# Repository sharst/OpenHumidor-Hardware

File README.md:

# OpenHumidor-Hardware
KiCad files of the OpenHumidor sensor PCB.
Files for 3D-printed humidifier parts, enclosures of the sensor board, etc.

Copyright 2016 Simon Harst

These files are licenced under the GPL v3 Licence, see LICENCE file.

I have included former versions of the PCB in separate folders. 

Versions 2 and 3 were created using the free version of EAGLE. Since version 4, boards are created with KICAD. 

## Ordering PCBs
The current version of the board is v0.6-mega. I'm currently testing all functions but minor bugs might still occur. If you're interested in trying out this project, you should consider contacting me.

So far, I have only ordered with two companies: 
* [PCB-pool](www.pcb-pool.de), located in Germany, the cheapest option takes about 2 weeks incl. shipping, you can directly upload the .kicad_pcb-file. 
* [Seeed Studio](http://www.seeedstudio.com/service/index.php?r=pcb), located in China and a lot cheaper (~14Euros for 10 pcbs). Takes about a month including shipping. You need to upload the .zip-file that's included in the gerber/ folder.

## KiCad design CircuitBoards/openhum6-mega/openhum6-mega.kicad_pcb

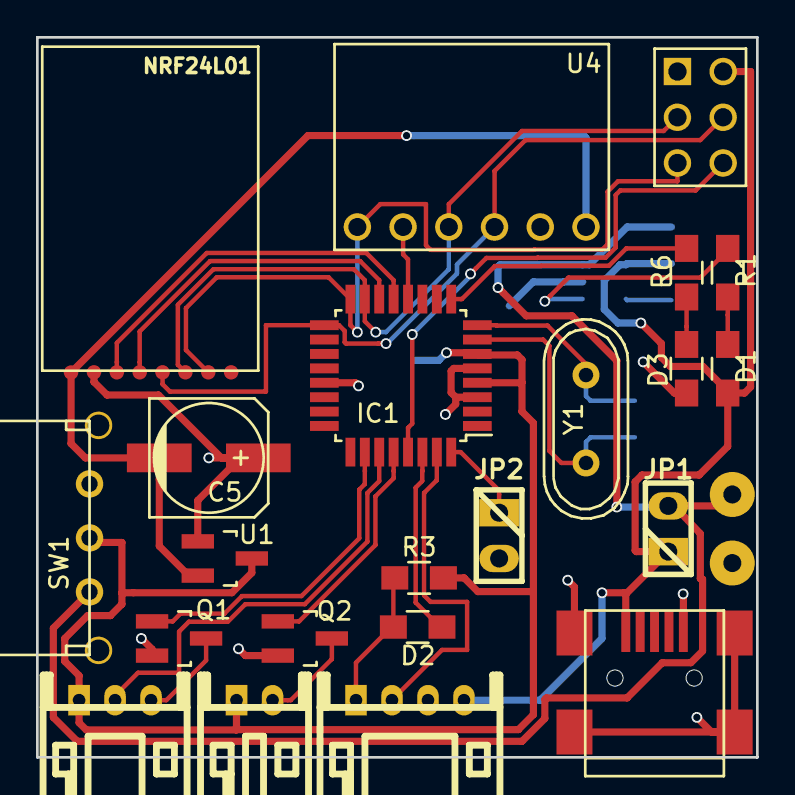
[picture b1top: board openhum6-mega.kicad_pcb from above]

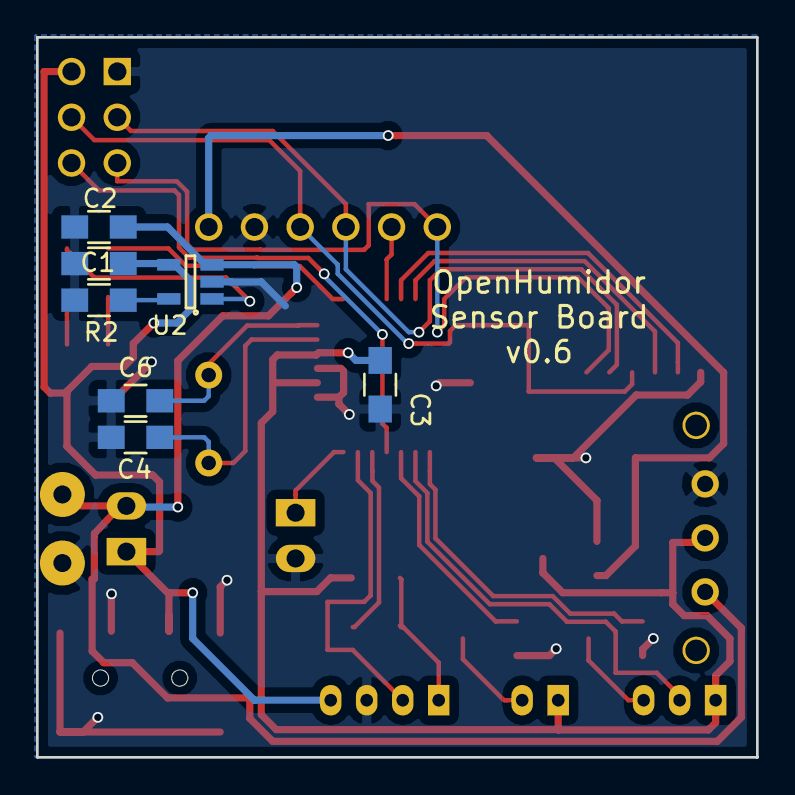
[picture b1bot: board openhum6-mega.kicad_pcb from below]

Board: 2 copper layers, 40.0 x 40.0 mm, 27 parts (7 on the bottom side), 24 nets.

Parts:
C1, C2: 4.7uF; R_0805_HandSoldering
C3: 100uF; R_0805_HandSoldering
C4, C6: 22pF; R_0805_HandSoldering
C5: 100uF; c_elec_6.3x5.3
CON1: USB-MINI-B; USB_Mini-B
D1: LED RED; R_0805_HandSoldering
D2: D; R_0805_HandSoldering
D3: LED GREEN; R_0805_HandSoldering
IC1: ATMEGA328P-A; TQFP-32_7x7mm_Pitch0.8mm
JP1, JP2: JUMPER; pin_strip_2
P1: ICSP; 2x3_pin_header
P2: BATTERY; solderpad2x
Q1, Q2: Q_NPN_BEC; SOT-23_Handsoldering
R1: 470; R_0805_HandSoldering
R2: 2k; R_0805_HandSoldering
R3: 1k; R_0805_HandSoldering
R6: 100; R_0805_HandSoldering
SW1: Switch_SPDT_x2; SS12F23
U1: MCP1700; SOT-23_Handsoldering
U2: MCP73831; SOT-23-5_handsoldering
U3: nRF24L01+; nrf24l01_mini
U4: BME280; BMP280
Y1: Crystal_Small; Crystal_HC49-U_Vertical

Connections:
+3V3: C5.2, U1.2, U3.1, U4.1
+5V: C1.2, CON1.1, D1.1, JP1.1, P1.2, U2.4
BAT+: C2.2, JP1.2, P2.1, SW1.1, U2.3
BAT-: C1.1, C2.1, C3.1, C4.1, C5.1, C6.1, CON1.5, CON1.6, D3.2, IC1.3, IC1.5, IC1.21, JP2.2, P1.1, P2.2, Q1.2, Q2.2, R2.1, SW1.3, U1.1, U2.2, U3.2, U4.2
HYG_CS: IC1.12, U4.5
MISO: IC1.16, P1.5, U3.7, U4.6
MOSI: IC1.15, P1.3, U3.6, U4.4
NRF_CE: IC1.13, U3.3
NRF_CSN: IC1.14, U3.4
unnamed: C4.2, IC1.7, Y1.1
unnamed: C6.2, IC1.8, Y1.2
unnamed: D1.2, R1.2
unnamed: D2.2, R3.1
unnamed: D3.1, R6.1
unnamed: IC1.9, R6.2
unnamed: R1.1, U2.1
unnamed: R2.2, U2.5
RESET: IC1.29, P1.6
SCK: IC1.17, P1.4, U3.5, U4.3
SENS_CALIB: IC1.32, JP2.1
SWITCH_FAN: IC1.28, Q2.1
SWITCH_MOIST: IC1.26, Q1.1
UART_RX: D2.1, IC1.30
VCC: C3.2, IC1.4, IC1.6, R3.2, SW1.2, U1.3

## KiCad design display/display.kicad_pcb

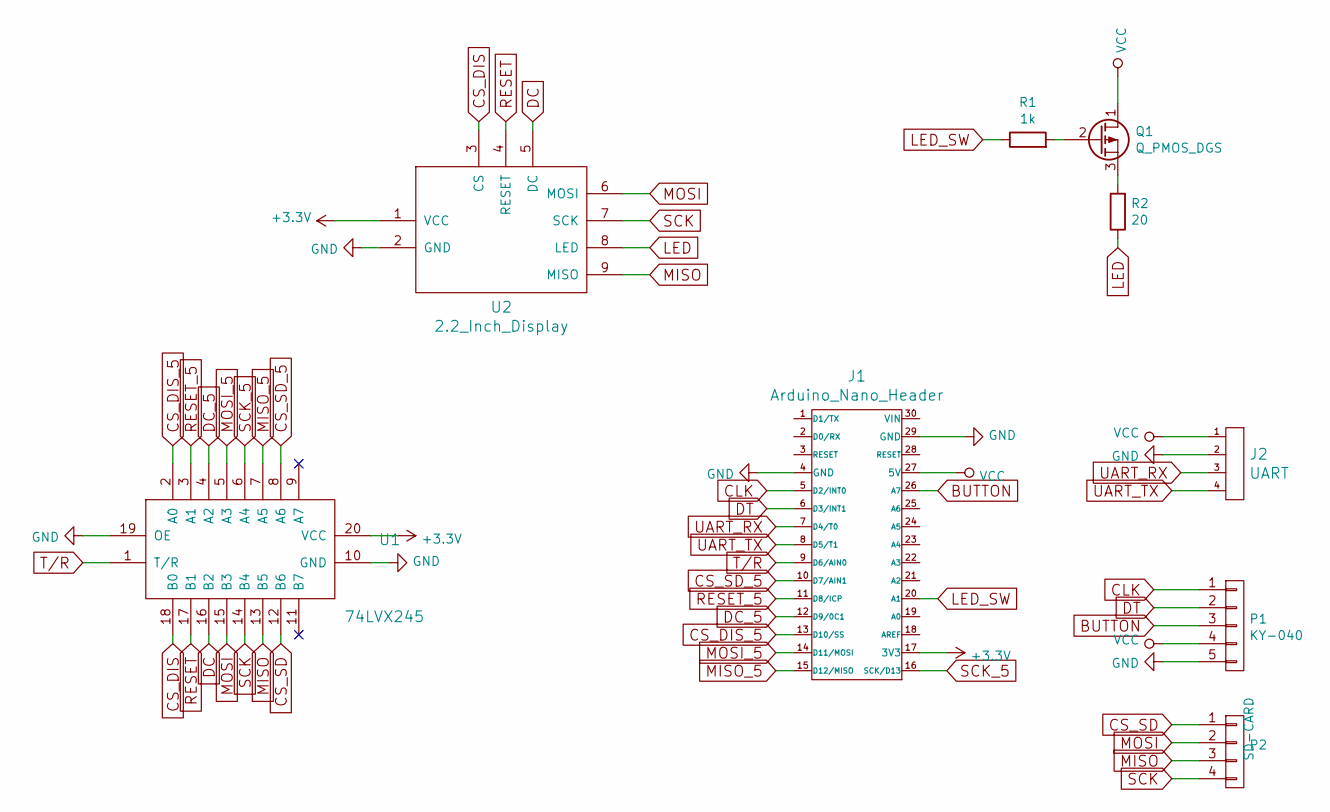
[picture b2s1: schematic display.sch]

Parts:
J1: Arduino_Nano_Header; arduino_nano_header
J2: UART; b4b-ph-kl
P1: KY-040; b5b-ph-kl
P2: SD-CARD; b4b-ph-kl
Q1: Q_PMOS_DGS; SOT-23_Handsoldering
R1: 1k; R_1206_HandSoldering
R2: 20; R_1206_HandSoldering
U1: 74LVX245; TSSOP20
U2: 2.2_Inch_Display; 2_2inch_display

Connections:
+3V3: J1.17 (3V3), U1.20 (VCC), U2.1 (VCC)
BUTTON: J1.26 (A7), P1.3
CLK: J1.5 (D2/INT0), P1.1
CS_DIS: U1.18 (B0), U2.3 (CS)
CS_DIS_5: J1.13 (D10/SS), U1.2 (A0)
CS_SD: P2.1, U1.12 (B6)
CS_SD_5: J1.10 (D7/AIN1), U1.8 (A6)
DC: U1.16 (B2), U2.5 (DC)
DC_5: J1.12 (D9/0C1), U1.4 (A2)
DT: J1.6 (D3/INT1), P1.2
GND: J1.4 (GND), J1.29 (GND), J2.2, P1.5, U1.10 (GND), U1.19 (OE), U2.2 (GND)
LED: R2.1, U2.8 (LED)
LED_SW: J1.20 (A1), R1.1
MISO: P2.3, U1.13 (B5), U2.9 (MISO)
MISO_5: J1.15 (D12/MISO), U1.7 (A5)
MOSI: P2.2, U1.15 (B3), U2.6 (MOSI)
MOSI_5: J1.14 (D11/MOSI), U1.5 (A3)
unnamed: Q1.2 (G), R1.2
unnamed: Q1.3 (S), R2.2
RESET: U1.17 (B1), U2.4 (RESET)
RESET_5: J1.11 (D8/ICP), U1.3 (A1)
SCK: P2.4, U1.14 (B4), U2.7 (SCK)
SCK_5: J1.16 (SCK/D13), U1.6 (A4)
T/R: J1.9 (D6/AIN0), U1.1 (T/R)
UART_RX: J1.7 (D4/T0), J2.3
UART_TX: J1.8 (D5/T1), J2.4
VCC: J1.27 (5V), J2.1, P1.4, Q1.1 (D)

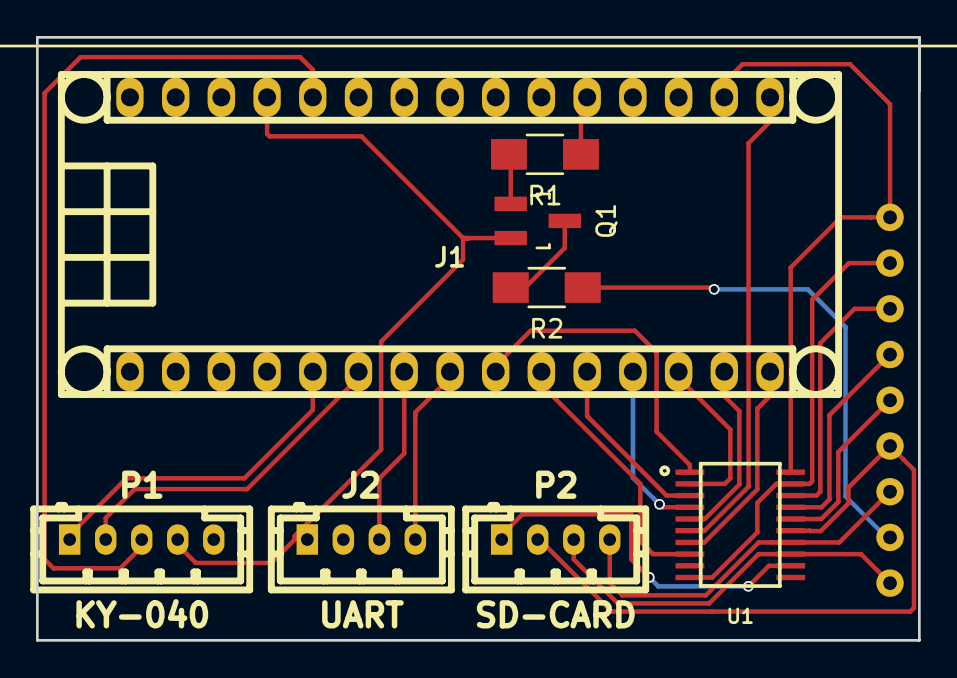
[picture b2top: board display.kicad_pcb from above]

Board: 2 copper layers, 49.0 x 33.5 mm, 9 parts (0 on the bottom side), 27 nets.

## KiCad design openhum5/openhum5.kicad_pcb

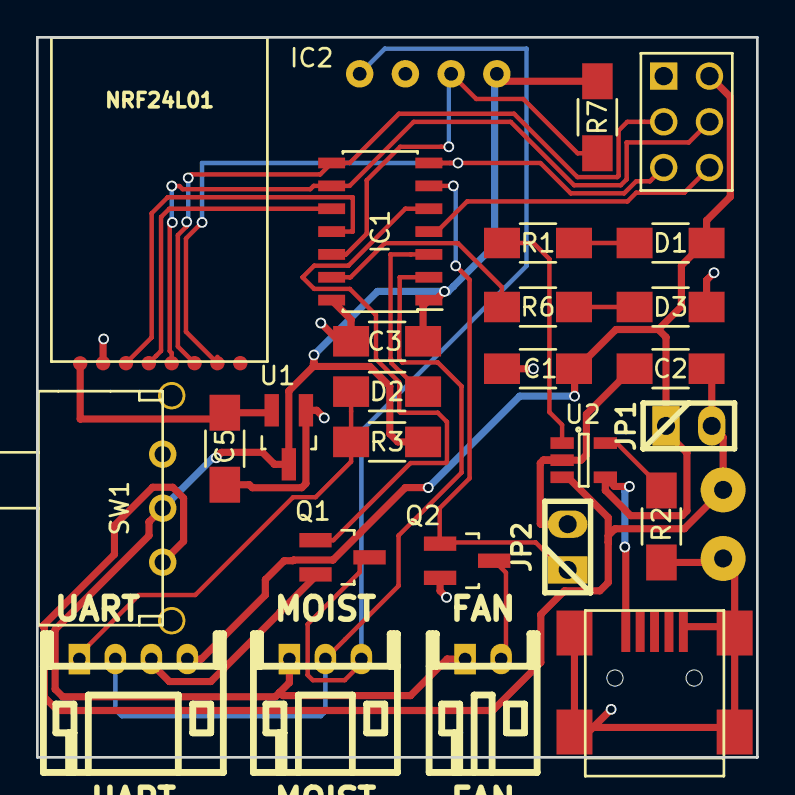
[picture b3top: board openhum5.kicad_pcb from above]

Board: 2 copper layers, 40.0 x 40.0 mm, 28 parts (0 on the bottom side), 24 nets.

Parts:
C1, C2: 4.7uF; R_1206_HandSoldering
C3, C5: 100uF; R_1206_HandSoldering
CON1: USB-MINI-B; USB_Mini-B
D1: LED RED; R_1206_HandSoldering
D2: D; R_1206_HandSoldering
D3: LED GREEN; R_1206_HandSoldering
FAN: FAN; s2b-ph-kl
IC1: ATTINY84A-SS; SOIC-14_3.9x8.7mm_Pitch1.27mm
IC2: DHT22
JP1, JP2: JUMPER; pin_strip_2
MOIST: MOIST; s3b-ph-kl
P1: ICSP; 2x3_pin_header
P2: BATTERY; solderpad2x
Q1, Q2: Q_NPN_BEC; SOT-23_Handsoldering
R1: 470; R_1206_HandSoldering
R2: 2k; R_1206_HandSoldering
R3: 1k; R_1206_HandSoldering
R6, R7: 100; R_1206_HandSoldering
SW1: Switch_SPDT_x2; SS12F23
U1: MCP1700; SOT-23_Handsoldering
U2: MCP73831; SOT-23-5_handsoldering
U3: nRF24L01+; nrf24l01_mini
UART: UART; s4b-ph-kl

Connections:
+3V3: C5.2, U1.2, U3.1
+5V: C1.2, CON1.1, D1.1, JP1.1, P1.2, U2.4, UART.4
BAT+: C2.2, JP1.2, P2.1, SW1.1, U2.3
BAT-: C1.1, C2.1, C3.2, C5.1, CON1.5, CON1.6, D3.2, IC1.14, JP2.2, P1.1, P2.2, Q1.2, Q2.2, R2.1, SW1.3, U1.1, U2.2, U3.2, UART.3
DATA_HYGRO: IC1.12, IC2.2, R7.1
DATA_MOIST: IC1.2, MOIST.2, UART.2
MISO: IC1.7, P1.5, U3.7
MOSI: IC1.8, P1.3, U3.6
NRF_CE: IC1.11, U3.3
NRF_CSN: IC1.10, U3.4
unnamed: D1.2, R1.2
unnamed: D2.2, R3.1, UART.1
unnamed: D3.1, R6.1
unnamed: IC1.13, R6.2
unnamed: IC2.4, MOIST.3, Q1.3
unnamed: FAN.2, Q2.3
unnamed: R1.1, U2.1
unnamed: R2.2, U2.5
RESET: IC1.4, P1.6
SCK: IC1.9, P1.4, U3.5
SENS_CALIB: IC1.6, JP2.1, Q2.1
SWITCH_MOIST: IC1.5, Q1.1
UART_RX: D2.1, IC1.3
VCC: C3.1, FAN.1, IC1.1, IC2.1, MOIST.1, R3.2, R7.2, SW1.2, U1.3

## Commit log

2016-01-14 First commit of OpenHumidor PCB project
2016-01-16 Added BOM for OpenHumidor v4
2016-03-12 File version updates to board v5. Added board for new arduino nano base station
2016-06-01 First production version of display PCB
2016-08-13 Newest version of openhumidor board: v0.6
2016-08-13 Add production drawings of PCB
2016-08-13 First STL version of humidifiers.
2016-08-13 Reorganized repository; added sketchup and STL files + lots of documentation
2016-08-22 Added gaps for printing, added battery pack
